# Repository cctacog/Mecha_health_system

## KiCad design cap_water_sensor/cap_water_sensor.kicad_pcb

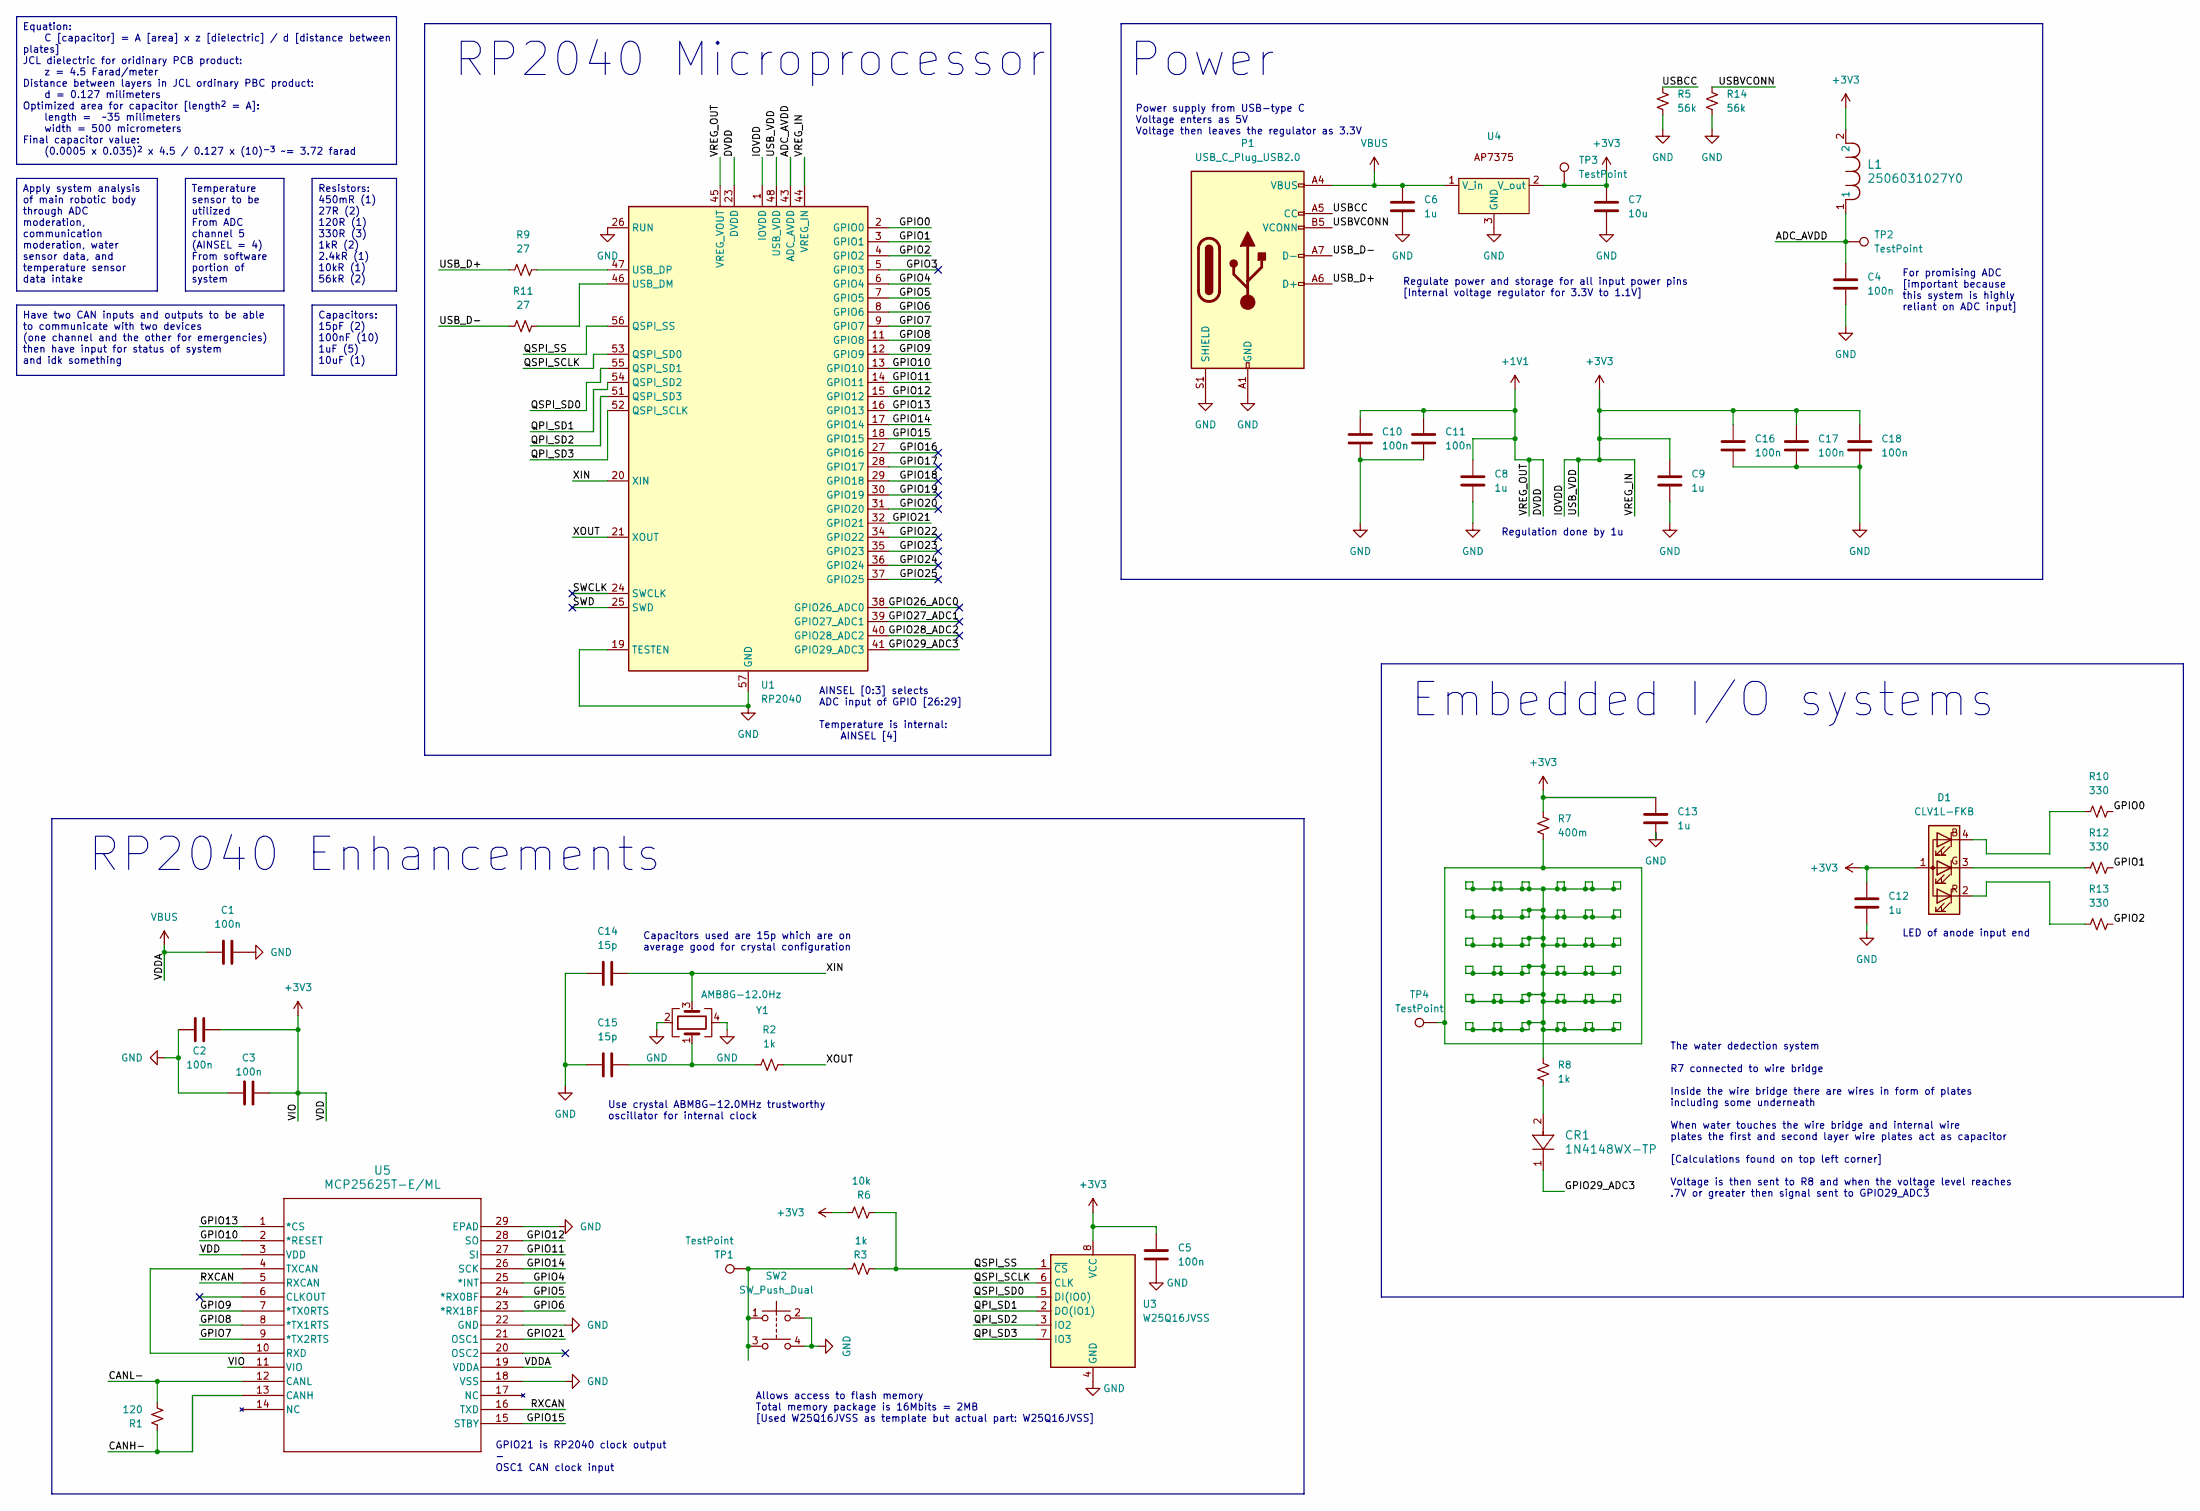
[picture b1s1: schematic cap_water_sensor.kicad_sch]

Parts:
C1, C2, C3, C4, C5, C10, C11, C16, C17, C18: 100n; C_0805_2012Metric
C6, C8, C9, C12, C13: 1u; C_0805_2012Metric
C7: 10u; C_0805_2012Metric
C14, C15: 15p; C_0805_2012Metric
CR1: 1N4148WX-TP; CR_SOD323_MCC
D1: CLV1L-FKB; LED_Cree-PLCC4_3.2x2.8mm_CCW
L1: 2506031027Y0; L_0603_1608Metric
P1: USB_C_Plug_USB2.0; USB_C_Receptacle_GCT_USB4105-xx-A_16P_TopMnt_Horizontal
R1: 120; R_0805_2012Metric
R2, R3, R8: 1k; R_0805_2012Metric
R5, R14: 56k; R_0805_2012Metric
R6: 10k; R_0805_2012Metric
R7: 400m; R_0805_2012Metric
R9, R11: 27; R_0805_2012Metric
R10, R12, R13: 330; R_0805_2012Metric
SW2: SW_Push_Dual; SW_Push_1P1T_NO_6x6mm_H9.5mm
TP1, TP2, TP3, TP4: TestPoint; TestPoint_Pad_1.5x1.5mm
U1: RP2040; QFN-56-1EP_7x7mm_P0.4mm_EP3.2x3.2mm
U3: W25Q16JVSS; SOIC-8_5.23x5.23mm_P1.27mm
U4: TSOT-23
U5: MCP25625T-E/ML; QFN-28-1EP_6x6mm_P0.65mm_EP4.8x4.8mm
Y1: AMB8G-12.0Hz; XTAL_ABM8G-12.000MHZ-4Y-T3

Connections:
+1V1: C8.1, C10.1, C11.1, U1.23 (DVDD), U1.45 (VREG_VOUT), U1.50 (DVDD)
+3V3: C2.2, C3.2, C5.1, C7.1, C9.1, C12.1, C13.1, C16.1, C17.1, C18.1, D1.1 (A), L1.2, R6.1, R7.1, TP3.1, U1.1 (IOVDD), U1.10 (IOVDD), U1.22 (IOVDD), U1.33 (IOVDD), U1.42 (IOVDD), U1.44 (VREG_IN), U1.48 (USB_VDD), U1.49 (IOVDD), U3.8 (VCC), U4.2 (V_out), U5.3 (VDD), U5.11 (VIO)
/ADC_AVDD: C4.1, L1.1, TP2.1, U1.43 (ADC_AVDD)
/CANH-: R1.1, U5.13 (CANH)
/CANL-: R1.2, U5.12 (CANL)
/GPIO0: R10.2, U1.2 (GPIO0)
/GPIO1: R12.2, U1.3 (GPIO1)
/GPIO2: R13.2, U1.4 (GPIO2)
/GPIO3: U1.5 (GPIO3)
/GPIO4: U1.6 (GPIO4), U5.25 (*INT)
/GPIO5: U1.7 (GPIO5), U5.24 (*RX0BF)
/GPIO6: U1.8 (GPIO6), U5.23 (*RX1BF)
/GPIO7: U1.9 (GPIO7), U5.9 (*TX2RTS)
/GPIO8: U1.11 (GPIO8), U5.8 (*TX1RTS)
/GPIO9: U1.12 (GPIO9), U5.7 (*TX0RTS)
/GPIO10: U1.13 (GPIO10), U5.2 (*RESET)
/GPIO11: U1.14 (GPIO11), U5.27 (SI)
/GPIO12: U1.15 (GPIO12), U5.28 (SO)
/GPIO13: U1.16 (GPIO13), U5.1 (*CS)
/GPIO14: U1.17 (GPIO14), U5.26 (SCK)
/GPIO15: U1.18 (GPIO15), U5.15 (STBY)
/GPIO16: U1.27 (GPIO16)
/GPIO17: U1.28 (GPIO17)
/GPIO18: U1.29 (GPIO18)
/GPIO19: U1.30 (GPIO19)
/GPIO20: U1.31 (GPIO20)
/GPIO21: U1.32 (GPIO21), U5.21 (OSC1)
/GPIO22: U1.34 (GPIO22)
/GPIO23: U1.35 (GPIO23)
/GPIO24: U1.36 (GPIO24)
/GPIO25: U1.37 (GPIO25)
/GPIO26_ADC0: U1.38 (GPIO26_ADC0)
/GPIO27_ADC1: U1.39 (GPIO27_ADC1)
/GPIO28_ADC2: U1.40 (GPIO28_ADC2)
/GPIO29_ADC3: CR1.1, U1.41 (GPIO29_ADC3)
/QPI_SD1: U1.54 (QSPI_SD2), U3.2 (DO(IO1))
/QPI_SD2: U1.51 (QSPI_SD3), U3.3 (IO2)
/QPI_SD3: U1.52 (QSPI_SCLK), U3.7 (IO3)
/QSPI_SCLK: U1.53 (QSPI_SD0), U3.6 (CLK)
/QSPI_SD0: U1.55 (QSPI_SD1), U3.5 (DI(IO0))
/QSPI_SS: R3.2, R6.2, U1.56 (QSPI_SS), U3.1 (~CS)
/RXCAN: U5.5 (RXCAN), U5.16 (TXD)
/SWCLK: U1.24 (SWCLK)
/SWD: U1.25 (SWD)
/USBCC: P1.A5 (CC), R5.1
/USBVCONN: P1.B5 (VCONN), R14.1
/USB_D+: P1.A6 (D+), R9.1
/USB_D-: P1.A7 (D-), R11.1
/XIN: C14.2, U1.20 (XIN), Y1.3
/XOUT: R2.2, U1.21 (XOUT)
GND: C1.2, C2.1, C3.1, C4.2, C5.2, C6.2, C7.2, C8.2, C9.2, C10.2, C11.2, C12.2, C13.2, C14.1, C15.1, C16.2, C17.2, C18.2, P1.A1 (GND), P1.A12 (GND), P1.B1 (GND), P1.B12 (GND), P1.S1 (SHIELD), R5.2, R14.2, SW2.2, SW2.4, U1.19 (TESTEN), U1.26 (RUN), U1.57 (GND), U3.4 (GND), U4.3 (GND), U5.18 (VSS), U5.22 (GND), U5.29 (EPAD), Y1.2, Y1.4
unnamed: C15.2, R2.1, Y1.1
unnamed: CR1.2, R8.2
unnamed: D1.4 (BK), R10.1
unnamed: D1.3 (GK), R12.1
unnamed: D1.2 (RK), R13.1
unnamed: R3.1, SW2.1, SW2.3, TP1.1
unnamed: R7.2, TP4.1
unnamed: R11.2, U1.46 (USB_DM)
unnamed: R9.2, U1.47 (USB_DP)
unnamed: U5.4 (TXCAN), U5.10 (RXD)
VBUS: C1.1, C6.1, P1.A4 (VBUS), P1.A9 (VBUS), P1.B4 (VBUS), P1.B9 (VBUS), U4.1 (V_in), U5.19 (VDDA)

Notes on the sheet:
Capacitors: 15pF (2) 100nF (10) 1uF (5) 10uF (1)
Equation: C [capacitor] = A [area] x z [dielectric] / d [distance between plates] JCL dielectric for oridinary PCB product: z = 4.5 Farad/meter Distance between layers in JCL ordinary PBC product: d = 0.127 milimeters Optimized area for capacitor [length^{2} = A]: length = ~35 milimeters width = 50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
Resistors: 450mR (1) 27R (2) 120R (1) 330R (3) 1kR (2) 2.4kR (1) 10kR (1) 56kR (2)
Have two CAN inputs and outputs to be able to communicate with two devices (one channel and the other for emergencies) then have input for status of system and idk something
Apply system analysis of main robotic body through ADC moderation, communication moderation, water sensor data, and temperature sensor data intake
Temperature sensor to be utilized From ADC channel 5 (AINSEL = 4) From software portion of system
Regulation done by 1u
RP2040 Microprocessor
GPIO21 is RP2040 clock output - OSC1 CAN clock input
AINSEL [0:3] selects ADC input of GPIO [26:29] Temperature is internal: AINSEL [4]
For promising ADC [important because this system is highly reliant on ADC input]
Power supply from USB-type C Voltage enters as 5V Voltage then leaves the regulator as 3.3V
Allows access to flash memory Total memory package is 16Mbits = 2MB [Used W25Q16JVSS as template but actual part: W25Q16JVSS]
RP2040 Enhancements
Use crystal ABM8G-12.0MHz trustworthy oscillator for internal clock
Embedded I/O systems
Capacitors used are 15p which are on average good for crystal configuration
The water dedection system R7 connected to wire bridge Inside the wire bridge there are wires in form of plates including some underneath When water touches the wire bridge and internal wire plates the first and second layer wire plates act as capacitor [Calculations found on top left corner] Volta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
LED of anode input end
Regulate power and storage for all input power pins [Internal voltage regulator for 3.3V to 1.1V]
Power

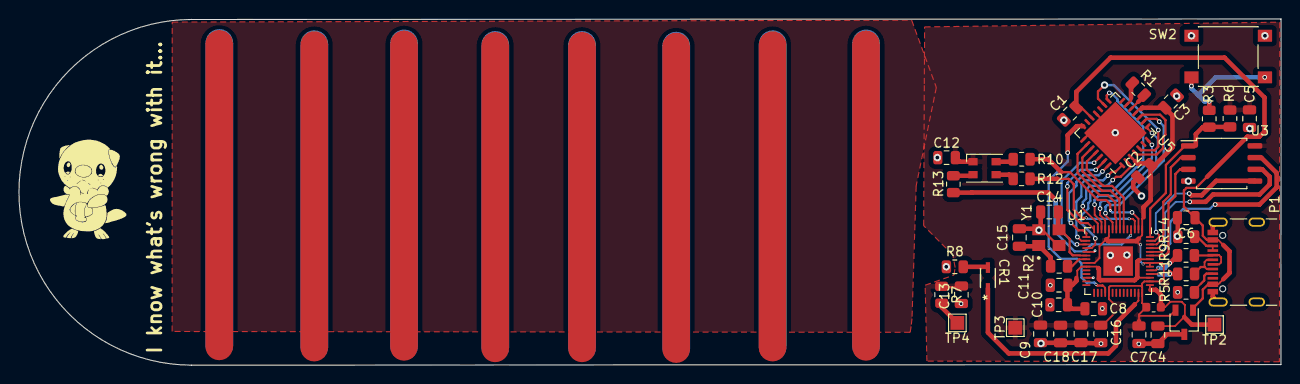
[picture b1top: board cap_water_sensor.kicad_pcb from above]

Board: 2 copper layers, 136.6 x 37.5 mm, 45 parts (0 on the bottom side), 47 nets.

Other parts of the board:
G: LOGO; oshowatt

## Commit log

2024-03-04 files to be added for pcb and schem
2024-03-04 reorganization
2024-03-04 reorganication_
2024-03-07 changed sims and edits to pcb
2024-03-07 added version image
2024-03-07 cleaned the testing files
2024-03-07 edits to cap lining
2024-03-07 details to cap val of sim
2024-03-07 calculations for cap val and adjustments to wired caps
2024-03-09 PCB edits and code beginning
2024-03-09 changed name of folder bc... i can
2024-03-17 code edits and detail orientation; ;
2024-04-15 finally some code!
2024-04-25 edited the sensor platform
